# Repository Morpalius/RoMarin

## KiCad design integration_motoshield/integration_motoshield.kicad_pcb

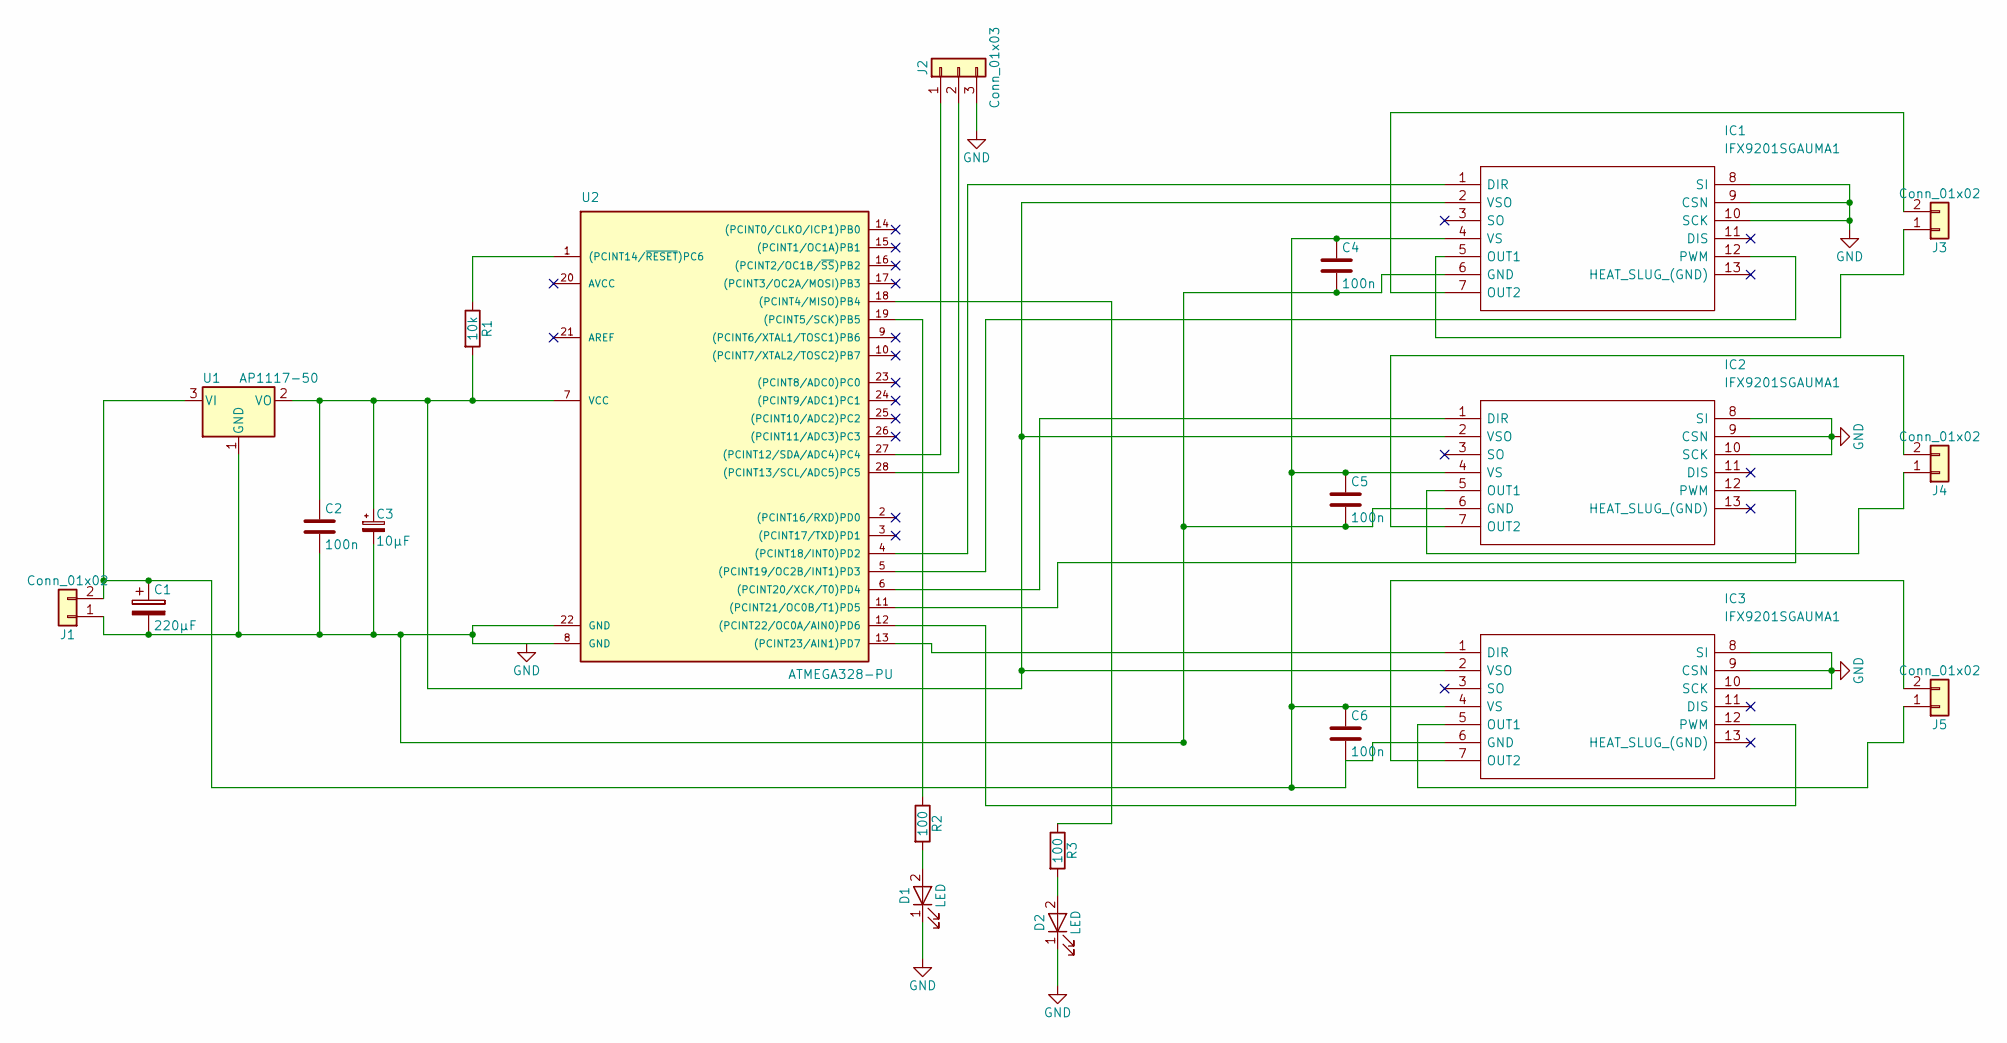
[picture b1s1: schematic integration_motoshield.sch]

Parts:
C1: 220µF; CP_Radial_Tantal_D5.0mm_P2.50mm
C2, C4, C5, C6: 100n; C_Disc_D5.0mm_W2.5mm_P2.50mm
C3: 10µF; condo_D8mm_P3mm
D1, D2: LED; LED_D3.0mm_Horizontal_O1.27mm_Z2.0mm
IC1, IC2, IC3: IFX9201SGAUMA1; IFX9201SG; Manufacturer_Part_Number IFX9201SGAUMA1
J1, J3, J4, J5: Conn_01x02; bornier2x2.54mm
J2: Conn_01x03; bornier3x2.54mm
R1: 10k; R_Axial_DIN0207_L6.3mm_D2.5mm_P7.62mm_Horizontal
R2, R3: 100; R_Axial_DIN0207_L6.3mm_D2.5mm_P7.62mm_Horizontal
U1: AP1117-50; TO-220
U2: ATMEGA328-PU; DIP-28_W7.62mm_Socket_LongPads

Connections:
unnamed: C1.1, C4.1, C5.1, C6.1, C6.2, IC1.4 (VS), IC2.4 (VS), IC3.4 (VS), IC3.6 (GND), J1.2, U1.3 (VI)
unnamed: C2.1, C3.1, IC1.2 (VSO), IC2.2 (VSO), IC3.2 (VSO), R1.2, U1.2 (VO), U2.7 (VCC)
unnamed: D1.2 (A), R2.2
unnamed: D2.2 (A), R3.2
unnamed: IC1.1 (DIR), U2.4 ((PCINT18/INT0)PD2)
unnamed: IC1.5 (OUT1), J3.1
unnamed: IC1.7 (OUT2), J3.2
unnamed: IC1.12 (PWM), U2.5 ((PCINT19/OC2B/INT1)PD3)
unnamed: IC2.1 (DIR), U2.6 ((PCINT20/XCK/T0)PD4)
unnamed: IC2.5 (OUT1), J4.1
unnamed: IC2.7 (OUT2), J4.2
unnamed: IC2.12 (PWM), U2.11 ((PCINT21/OC0B/T1)PD5)
unnamed: IC3.1 (DIR), U2.13 ((PCINT23/AIN1)PD7)
unnamed: IC3.5 (OUT1), J5.1
unnamed: IC3.7 (OUT2), J5.2
unnamed: IC3.12 (PWM), U2.12 ((PCINT22/OC0A/AIN0)PD6)
unnamed: J2.1, U2.27 ((PCINT12/SDA/ADC4)PC4)
unnamed: J2.2, U2.28 ((PCINT13/SCL/ADC5)PC5)
unnamed: R1.1, U2.1 ((PCINT14/~RESET~)PC6)
unnamed: R2.1, U2.19 ((PCINT5/SCK)PB5)
unnamed: R3.1, U2.18 ((PCINT4/MISO)PB4)

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
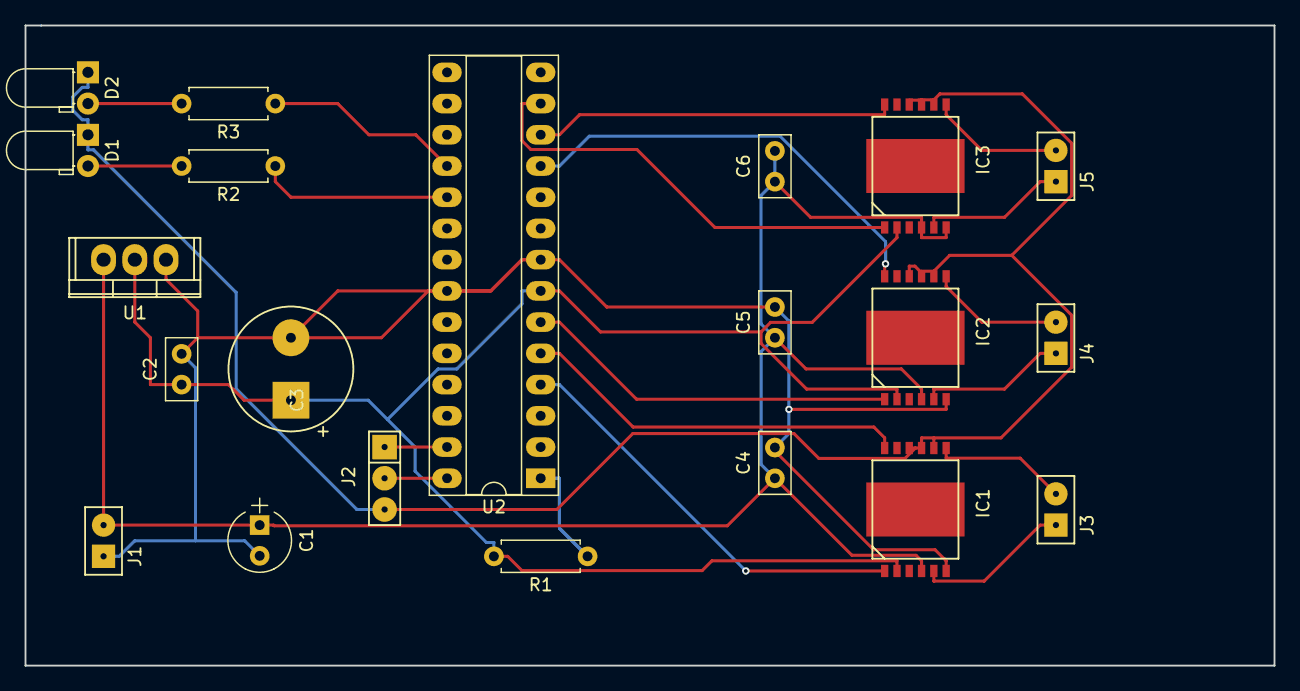
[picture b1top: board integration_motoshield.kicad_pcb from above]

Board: 2 copper layers, 101.6 x 52.1 mm, 21 parts (0 on the bottom side), 23 nets.
